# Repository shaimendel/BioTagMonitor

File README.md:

# Software, Firmware, and Hardware for a Battery Characterization System
Biological tags are very popular in the field of animal behaviour research.
These tags developers have to deal with numerous problems, both in hardware and software.
One of the problems is to choose the correct battery to put within the tag itself: the battery should be lightweight, to last long, to cope with different weather conditions, etc.
Until now, the setup and procedure of comparing different batteries performance included:
- A mocked tag: A dedicated circuit that used the battery in the same way the tag does
- The battery itself
- Scope and other expensive equipment to measure the voltage and current along time

This procedure is long, expensive and uncomfortable.
This project concentrates on biological tags that are put on birds, these tags send a short pulse (8-10ms) of location every ~1 second.

## Goal
This project implements an arduino and PC software that communicate with each other and make the entire procedure very easy, cheap and quick.
The project contains:
- Various arduino softwares for different needs
- A PC software (C#) that operates the arduino and logs the measurements
- A PC software (Python) for visualization

## Content

### Visualization
- createData.py: Creates a mock log file with mocked measurements
- visualizeData.py: Measurements visualization utility

### Measure
The C# project that operates the arduino, both for tag simulation and also with real tags.
In order to compile Measure.csproj to mono: 
- cd to Measure.csproj folder
- xbuild /p:TargetFrameworkVersion="v4.5"

#### AutoMeasureGraphMin
Arduino software to measure bio tags.
This software communicates with the PC software and sends the measurements to it.
Supports 2 modes:
- Simulation: The sofware simulates tag behaviour and measures the battery performance in pulses along time
- Real tag: Measurement of real tag pulses. This mode contains a pulse identification algorithm, becuase the tag itself produces the pulses.

#### AutoMeasureGraphStart
Arduino software to measure bio tags in a situation the tag fails to start.
This software records measurements as soon as it identifies an activity in the tag and sends it to the PC software

#### PCB
Circuit and printed-circut board design for the add-on analog board. These are Eagle 6.6 files. The "relabeled" schmatics is cleaned up a bit for clarity. It also does not include 0-Ohm resistors and jumper traces that are included in the original design to allow patching the board. 

#### Simulation
LTSpice simulation model for the analysis of the reservoir cap and its limiter resistor.

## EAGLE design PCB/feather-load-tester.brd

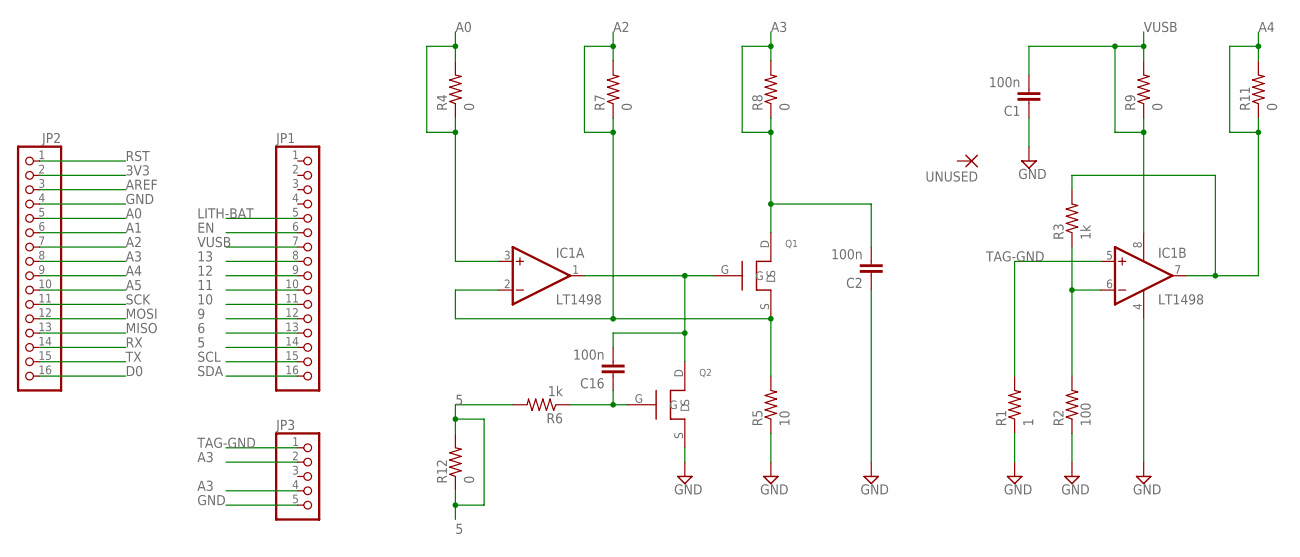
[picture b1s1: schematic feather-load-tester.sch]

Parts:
C1, C2, C16: 100n; 0805-CAP
IC1: LT1498; SO08
JP1, JP2: PINHD-1X16; 1X16
JP3: PINHD-1X5; 1X05
Q1, Q2: NMOSFET_SC59; SC59
R1: 1; 0805
R2: 100; 0805
R3, R6: 1k; 0805
R4, R7, R8, R9, R11, R12: 0; 0805
R5: 10; 0805
UNUSED: SMD2; SMD1,27-2,54

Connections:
3V3: JP2.2
5: JP1.14, R6.2, R12.1, R12.2
6: JP1.13
9: JP1.12
10: JP1.11
11: JP1.10
12: JP1.9
13: JP1.8
A0: IC1.3 (+IN), JP2.5, R4.1, R4.2
A1: JP2.6
A2: IC1.2 (-IN), JP2.7, Q1.S, R5.2, R7.1, R7.2
A3: C2.2, JP2.8, JP3.2, JP3.4, Q1.D, R8.1, R8.2
A4: IC1.7 (OUT), JP2.9, R3.2, R11.1, R11.2
A5: JP2.10
AREF: JP2.3
D0: JP2.16
EN: JP1.6
GND: C1.1, C2.1, IC1.4 (V-), JP2.4, JP3.5, Q2.S, R1.1, R2.1, R5.1
LITH-BAT: JP1.5
MISO: JP2.13
MOSI: JP2.12
unnamed: IC1.6 (-IN), R2.2, R3.1
unnamed: C16.1, Q2.G, R6.1
unnamed: C16.2, IC1.1 (OUT), Q1.G, Q2.D
RST: JP2.1
RX: JP2.14
SCK: JP2.11
SCL: JP1.15
SDA: JP1.16
TAG-GND: IC1.5 (+IN), JP3.1, R1.2
TX: JP2.15
VUSB: C1.2, IC1.8 (V+), JP1.7, R9.1, R9.2

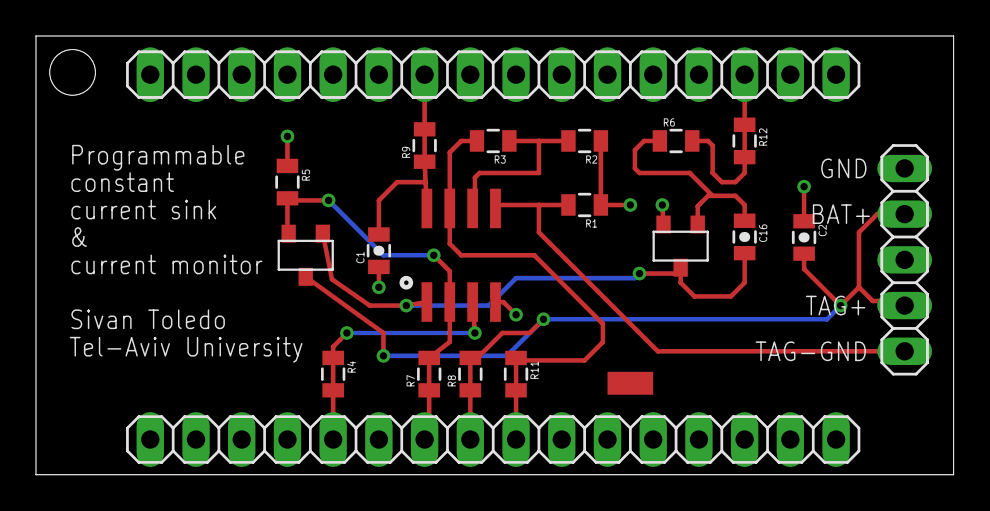
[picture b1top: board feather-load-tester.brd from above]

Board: 2 copper layers, 51.0 x 24.4 mm, 21 parts (0 on the bottom side), 11 nets.

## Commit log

2018-07-07 All files were added
2018-07-07 Updated .gitignore
2018-07-07 Added simulation check box (to support both simulation tags and real tags)
2018-07-07 Don't start the simulation task before the go button is pressed
2018-08-01 Added AutoMeasureGraphMin.ino: Code that automatically recognizes pulses
2018-08-01 Removed usage of libmaple in order to compile on M3 Express
2018-08-01 cross platform pinouts
2018-08-12 On non-simulation: Read from TAG_LOAD_CURRENT. M4 Express: Set analog read resolution to 12 bits
2018-08-25 Added sampling during pulse. Added voltage sampling during rest
2018-08-25 Unified the simulated tag ino and the real tag ino
2018-09-01 Added support in never lasting pulses. Added python utilities for creating mock data and for visualization
2018-09-01 Better handle samples before pulse
2018-09-02 Fixed simulated_tag.cpp values
2018-09-17 Minor fixes
2018-09-29 Fixed recording of samples before pulse
2018-10-06 visualizeData.py: Added os flag + if the log contains a single sample than show it
2018-10-06 Added AutoMeasureGraphStart.ino: A firmware that records a tag from the time a "pulse" is beginning
2018-10-21 More references and citations.
2018-11-03 Mini bug fix
2018-11-07 Added different y axis to current Divided current by 11
2018-11-17 Added the ability to recognize pulse start from voltage fall
2018-11-17 Added the precompiled linux binary
2018-11-21 Added the option to skip "potential bad pulses" (with the polarization symptom)
2023-12-05 added PCB files
2023-12-05 description of PCB directory
2023-12-06 copied from paper directory
2023-12-06 added a section on the simulation model

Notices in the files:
parts and their libraries:
SparkFun-Capacitors: Licensing: Creative Commons ShareAlike 4.0 International - https://creativecommons.org/licenses/by-sa/4.0
